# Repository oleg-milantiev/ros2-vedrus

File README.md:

# ros2-vedrus
ROS2 Vedrusohod bot sources

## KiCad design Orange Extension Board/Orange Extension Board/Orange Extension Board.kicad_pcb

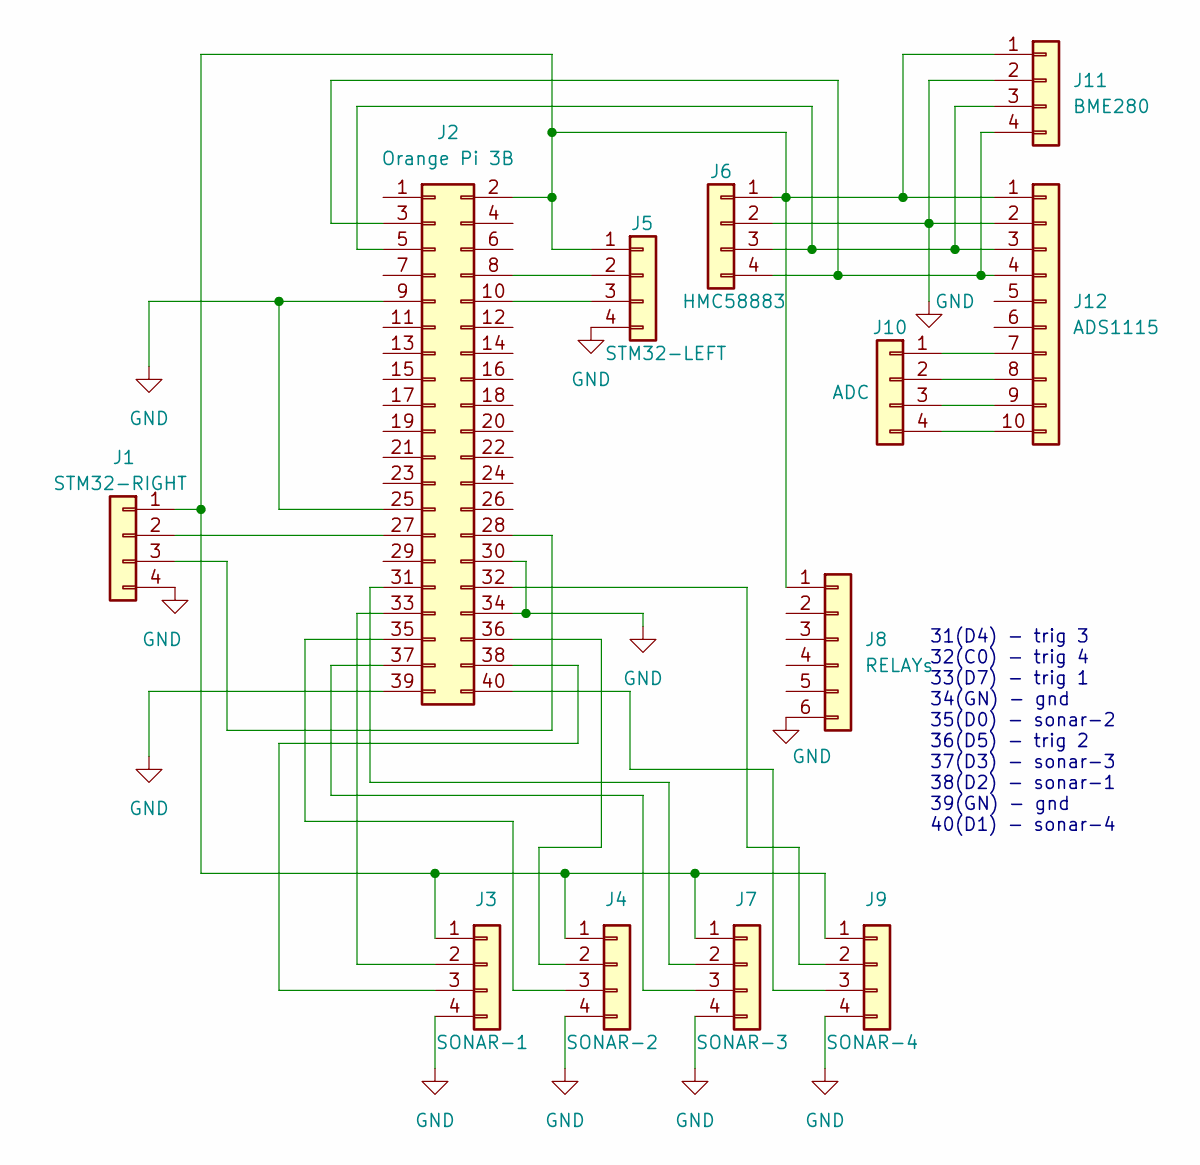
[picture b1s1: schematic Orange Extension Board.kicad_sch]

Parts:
J1: STM32-RIGHT; PinHeader_1x04_P2.54mm_Vertical
J2: Orange Pi 3B; PinHeader_2x20_P2.54mm_Vertical
J3: SONAR-1; PinHeader_1x04_P2.54mm_Vertical
J4: SONAR-2; PinHeader_1x04_P2.54mm_Vertical
J5: STM32-LEFT; PinHeader_1x04_P2.54mm_Vertical
J6: HMC58883; PinHeader_1x04_P2.54mm_Vertical
J7: SONAR-3; PinHeader_1x04_P2.54mm_Vertical
J8: RELAYs; PinHeader_1x06_P2.54mm_Vertical
J9: SONAR-4; PinHeader_1x04_P2.54mm_Vertical
J10: ADC; PinHeader_1x04_P2.54mm_Vertical
J11: BME280; PinHeader_1x04_P2.54mm_Vertical
J12: ADS1115; PinHeader_1x10_P2.54mm_Vertical

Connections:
GND: J1.4, J2.9, J2.25, J2.30, J2.34, J2.39, J3.4, J4.4, J5.4, J6.2, J7.4, J8.6, J9.4, J11.2, J12.2
unnamed: J1.1, J2.2, J3.1, J4.1, J5.1, J6.1, J7.1, J8.1, J9.1, J11.1, J12.1
unnamed: J1.2, J2.27
unnamed: J1.3, J2.28
unnamed: J2.3, J6.4, J11.4, J12.4
unnamed: J2.5, J6.3, J11.3, J12.3
unnamed: J2.8, J5.2
unnamed: J2.10, J5.3
unnamed: J2.32, J9.2
unnamed: J2.33, J3.2
unnamed: J2.40, J9.3
unnamed: J2.38, J3.3
unnamed: J2.36, J4.2
unnamed: J2.35, J4.3
unnamed: J2.31, J7.2
unnamed: J2.37, J7.3
unnamed: J10.1, J12.7
unnamed: J10.2, J12.8
unnamed: J10.3, J12.9
unnamed: J10.4, J12.10

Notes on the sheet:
31(D4) - trig 3 32(C0) - trig 4 33(D7) - trig 1 34(GN) - gnd 35(D0) - sonar-2 36(D5) - trig 2 37(D3) - sonar-3 38(D2) - sonar-1 39(GN) - gnd 40(D1) - sonar-4

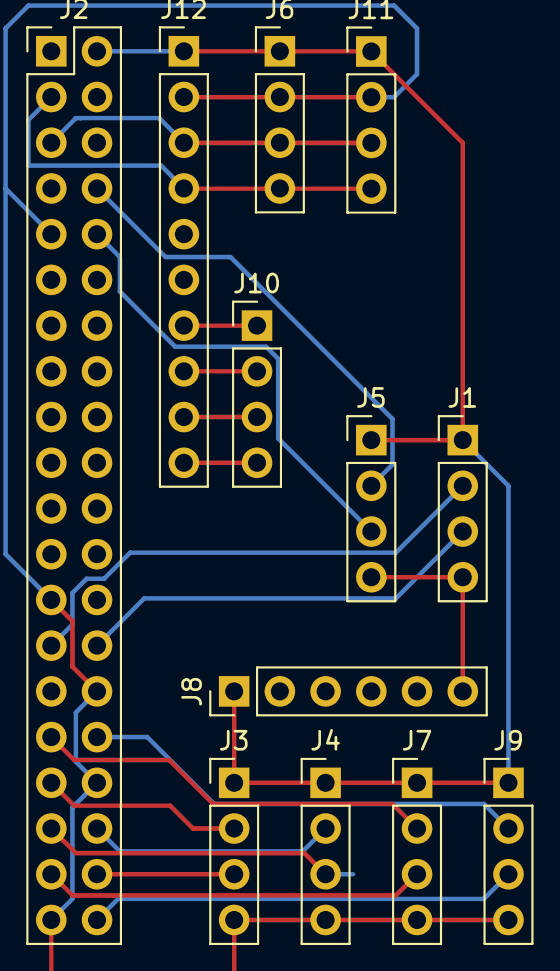
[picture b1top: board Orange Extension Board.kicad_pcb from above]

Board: 2 copper layers, 12 parts (0 on the bottom side), 20 nets.

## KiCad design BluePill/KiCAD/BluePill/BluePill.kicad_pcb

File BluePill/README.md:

# Blue Pill DC Motor Controller

This project implements a DC motor controller using the STM32F103C8T6 (Blue Pill) board. It features hardware quadrature encoder support, PID control, and serial communication for real-time control and monitoring.

## Features

- Hardware quadrature encoder support using STM32 Timer3
- 4x resolution encoder counting (both edges of both channels)
- PID-based motor speed control
- Serial communication at 115200 baud
- Real-time status reporting
- Configurable motor direction and speed
- Speed control in encoder ticks per second
- Hardware debouncing for reliable encoder readings

## Hardware Requirements

- STM32F103C8T6 (Blue Pill) board
- DC motor with quadrature encoder
- Motor driver (capable of DIR/PWM control)
- USB-to-Serial adapter (if not built into your programmer)

## Pin Connections

### Encoder
- Encoder A → PA6 (Timer3 Channel 1)
- Encoder B → PA7 (Timer3 Channel 2)

### Motor Control
- Direction → PA1
- PWM → PA2
- Brake → PA0 (TBD)

## Included Files

1. `Blink.ino` - Firmware for board testing
2. `BluePill.ino` - Main motor controller firmware
3. `Encoder.ino` - Test firmware for encoder verification
   - Supports one encoder:
     - Encoder 1: Timer3 (PA6/PA7)

## Software Requirements

1. Arduino IDE
2. STM32 board package for Arduino
3. PID_v1 library

## Installation

1. Install Arduino IDE from [arduino.cc](https://www.arduino.cc/en/software)
2. Install STM32 board package:
   https://github.com/stm32duino/Arduino_Core_STM32/wiki/Getting-Started
   - Open Arduino IDE
   - Go to Tools → Board → Boards Manager
   - Search for "STM32"
   - Install "STM32 MCU based boards"

3. Install PID Library:
   - Go to Tools → Manage Libraries
   - Search for "PID"
   - Install "PID" by Brett Beauregard

4. Configure Board Settings:
   - Board: "Generic STM32F103C series"
   - Upload Method: Your preferred method (ST-Link, Serial, etc.)
   - CPU Speed: "72MHz (Normal)"

5. Board Programming:
   - Set Boot0 jumper to 1
   - Connect board to computer
   - Press reset button on the board to prepare for upload
   - Click upload button in Arduino IDE
   - Set Boot0 jumper back to 0 (testing can be done without this step)

## Usage

### Serial Commands

The controller accepts the following commands through serial port at 115200 baud:

- `S` - Stop motor (sets target speed to 0)
- `M[speed]` - Move at specified speed (speed value depends on encoder resolution)
  - Positive values move forward
  - Negative values move reverse
  - Example: `M5` sets speed to 5 units forward
  - Example: `M-5` sets speed to 5 units reverse
- `X[max_pwm]` - Set maximum PWM value
  - Example: `X15` sets the maximum PWM value to 15

### Python Control Script

The project includes a Python script (`serial_control.py`) for easy motor control:

- Press 'S' to stop the motor
- Press '0-9' to set different speed levels (multiplied by 5)
- Press 'Q' to quit the program
- Real-time status messages are displayed automatically

To run the script:
```bash
python3 serial_control.py
```

### Status Messages

The controller sends status messages every 50ms in the following format:
```
SIDE,POS:[position],SPD:[current_speed],TGT:[target_speed],PWR:[motor_power],MAX_PWM:[max_pwm]
```

Where:
- `SIDE`: "VEDL" for left motor, "VEDR" for right motor
- `position`: Current encoder position (signed value, centered at 32767)
- `current_speed`: Actual speed in ticks/second
- `target_speed`: Commanded speed
- `motor_power`: PWM output (-PWR_MAX to PWR_MAX)
- `max_pwm`: Current maximum PWM value

## Hardware Configuration

- Encoder resolution: 8192 ticks per wheel revolution
- Maximum PWM value: 10
- Speed calculation interval: 50ms
- LED indication: PC13 lights up when speed exceeds half of encoder resolution

## Testing Encoder Hardware

The `Encoder.ino` firmware can be used to verify proper encoder operation:

1. Upload `Encoder.ino` to the BluePill
2. Open Serial Monitor at 115200 baud
3. Rotate encoder manually or using motor
4. Monitor the position values
   - Format: Single number representing encoder position
   - Values are centered around 0 (internally offset from 32767)
   - Positive values indicate one direction of rotation
   - Negative values indicate opposite direction
   - Updates every 100ms

Example output:
```
Hardware Encoder Test Started
Format: Encoder_Position
-123
-145
-160
0
42
85
```

Note: The position counter uses Timer3 in hardware quadrature mode with 4x resolution (counting both edges of both channels). The encoder connects to PA6 (Timer3 Channel 1) and PA7 (Timer3 Channel 2).

## PID Tuning

The default PID values are:
- Kp = 0.5
- Ki = 0.3
- Kd = 0.1

You may need to adjust these values based on your specific setup. To tune:
1. Start with all values at 0
2. Increase Kp until you get a reasonable response
3. Increase Ki to eliminate steady-state error
4. Add Kd to reduce overshoot if necessary

## Troubleshooting

1. **Motor doesn't move**:
   - Check power connections
   - Verify motor driver connections
   - Ensure PWM and DIR pins are correctly connected

2. **Encoder readings are erratic**:
   - Verify encoder connections match the Timer channels
   - Check encoder power supply
   - Ensure proper grounding
   - Verify encoder pull-up resistors are enabled

3. **Position counts in wrong direction**:
   - Swap encoder A and B connections
   - Or invert the motor power polarity

## License

This project is released under the MIT License. Feel free to use, modify, and distribute as needed.

---

# Контроллер двигателя постоянного тока на базе Blue Pill

Этот проект реализует контроллер двигателя постоянного тока с использованием платы STM32F103C8T6 (Blue Pill). Он включает в себя аппаратную поддержку квадратурного энкодера, ПИД-регулирование и последовательную связь для управления и мониторинга в реальном времени.

## Возможности

- Аппаратная поддержка квадратурного энкодера с использованием таймера STM32 Timer3
- Счетчик энкодера с 4-кратным разрешением (обе грани обоих каналов)
- ПИД-регулирование скорости двигателя
- Последовательная связь на скорости 115200 бод
- Отчеты о состоянии в реальном времени
- Настраиваемое направление и скорость двигателя
- Управление скоростью в тиках энкодера в секунду
- Аппаратное подавление дребезга для надежного считывания энкодера

## Аппаратные требования

- Плата STM32F103C8T6 (Blue Pill)
- Двигатель постоянного тока с квадратурным энкодером
- Драйвер двигателя (с управлением DIR/PWM)
- USB-Serial адаптер (если не встроен в программатор)
  (подключение https://microkontroller.ru/stm32-projects/nachalo-raboty-s-stm32-blue-pill-s-pomoshhyu-arduino-ide/ )

## Подключение выводов

### Энкодер
- Энкодер A → PA6 (Timer3 Channel 1)
- Энкодер B → PA7 (Timer3 Channel 2)

### Управление двигателем
- Направление → PA1
- ШИМ → PA2
- Тормоз → PA0 (TBD)

## Файлы в проекте

1. `Blink.ino` - Прошивка для проверки работы платы
2. `BluePill.ino` - Основная прошивка контроллера двигателя
3. `Encoder.ino` - Тестовая прошивка для проверки работы энкодера
   - Поддерживает один энкодер:
     - Энкодер 1: Timer3 (PA6/PA7)

## Программные требования

1. Arduino IDE
2. Пакет плат STM32 для Arduino
3. Библиотека PID_v1

## Установка

1. Установите Arduino IDE с [arduino.cc](https://www.arduino.cc/en/software)
2. Установите пакет плат STM32:
   https://github.com/stm32duino/Arduino_Core_STM32/wiki/Getting-Started
   - Откройте Arduino IDE
   - Перейдите в Инструменты → Плата → Менеджер плат
   - Найдите "STM32"
   - Установите "STM32 MCU based boards"

3. Установите библиотеку PID:
   - Перейдите в Инструменты → Управление библиотеками
   - Найдите "PID"
   - Установите "PID" от Brett Beauregard

4. Настройте параметры платы:
   - Плата: "Generic STM32F103C series"
   - Метод загрузки: Предпочитаемый метод (ST-Link, Serial и т.д.)
   - Частота CPU: "72MHz (Normal)"

5. Прошивка платы:
   - Переключить джампер Boot0 в 1
   - Подключить плату к компьютеру
   - Кнопкой сброса на плате подготовить плату к загрузке
   - Нажать кнопку загрузки в Arduino IDE
   - Переключить джампер Boot0 в 0 (тестировать можно без этого шага)

## Использование

### Команды последовательного порта

Контроллер принимает следующие команды через последовательный порт на скорости 115200 бод:

- `S` - Остановка двигателя (устанавливает целевую скорость в 0)
- `M[скорость]` - Движение с указанной скоростью (значение зависит от разрешения энкодера)
  - Положительные значения - движение вперед
  - Отрицательные значения - движение назад
  - Пример: `M5` устанавливает скорость 5 единиц вперед
  - Пример: `M-5` устанавливает скорость 5 единиц назад
- `X[max_pwm]` - Установить максимальное значение ШИМ
  - Пример: `X15` устанавливает максимальное значение ШИМ на 15

### Скрипт управления на Python

В проект включен Python-скрипт (`serial_control.py`) для удобного управления двигателем:

- Нажмите 'S' для остановки двигателя
- Нажмите '0-9' для установки различных уровней скорости (умножается на 5)
- Нажмите 'Q' для выхода из программы
- Сообщения о состоянии отображаются автоматически в реальном времени

Для запуска скрипта:
```bash
python3 serial_control.py
```

### Аппаратная конфигурация

- Разрешение энкодера: 8192 тика на оборот колеса
- Максимальное значение ШИМ: 10
- Интервал расчета скорости: 50мс
- Светодиодная индикация: PC13 загорается, когда скорость превышает половину разрешения энкодера

### Status Messages

The controller sends status messages every 50ms in the following format:
```
SIDE,POS:[position],SPD:[current_speed],TGT:[target_speed],PWR:[motor_power],MAX_PWM:[max_pwm]
```

Где:
- `SIDE`: "VEDL" для левого мотора, "VEDR" для правого мотора
- `position`: Текущая позиция энкодера (знаковое значение, центрировано на 32767)
- `current_speed`: Фактическая скорость в тиках в секунду
- `target_speed`: Заданная скорость
- `motor_power`: Выход ШИМ (от -PWR_MAX до PWR_MAX)
- `max_pwm`: Текущее максимальное значение ШИМ

## Тестирование энкодеров

Прошивка `Encoder.ino` может быть использована для проверки правильной работы энкодеров:

1. Загрузите `Encoder.ino` в BluePill
2. Откройте монитор порта на скорости 115200 бод
3. Вращайте энкодер вручную или с помощью двигателя
4. Отслеживайте значения позиций энкодера
   - Формат: Single number representing encoder position
   - Значения центрированы вокруг 0 (внутренне смещены от 32767)
   - Положительные значения указывают на одно направление вращения
   - Отрицательные значения указывают на противоположное направление
   - Обновляется каждые 100мс

Пример вывода:
```
Hardware Encoder Test Started
Format: Encoder_Position
-123
-145
-160
0
42
85
```

Примечание: Счетчик позиций использует Timer3 в режиме прямого квадратурного кодирования с 4x разрешением (подсчет обоих фронтов обоих каналов). Энкодер подключен к PA6 (Timer3 Channel 1) и PA7 (Timer3 Channel 2).

## Настройка ПИД-регулятора

Значения ПИД-регулятора по умолчанию:
- Kp = 0.5
- Ki = 0.3
- Kd = 0.1

Возможно, потребуется настроить эти значения под вашу конкретную установку. Для настройки:
1. Начните со всех значений равных 0
2. Увеличивайте Kp, пока не получите приемлемый отклик
3. Увеличивайте Ki для устранения статической ошибки
4. Добавьте Kd для уменьшения перерегулирования, если необходимо

## Устранение неполадок

1. **Двигатель не вращается**:
   - Проверьте подключение питания
   - Проверьте подключение драйвера двигателя
   - Убедитесь, что выводы ШИМ и DIR правильно подключены

2. **Показания энкодера нестабильны**:
   - Проверьте соответствие подключения энкодера каналам таймера
   - Проверьте питание энкодера
   - Обеспечьте правильное заземление
   - Проверьте включение подтягивающих резисторов

3. **Счетчик позиции работает в неправильном направлении**:
   - Поменяйте местами подключение выводов A и B энкодера
   - Или измените полярность питания двигателя

## Лицензия

Этот проект распространяется под лицензией MIT. Вы можете свободно использовать, изменять и распространять его по необходимости.

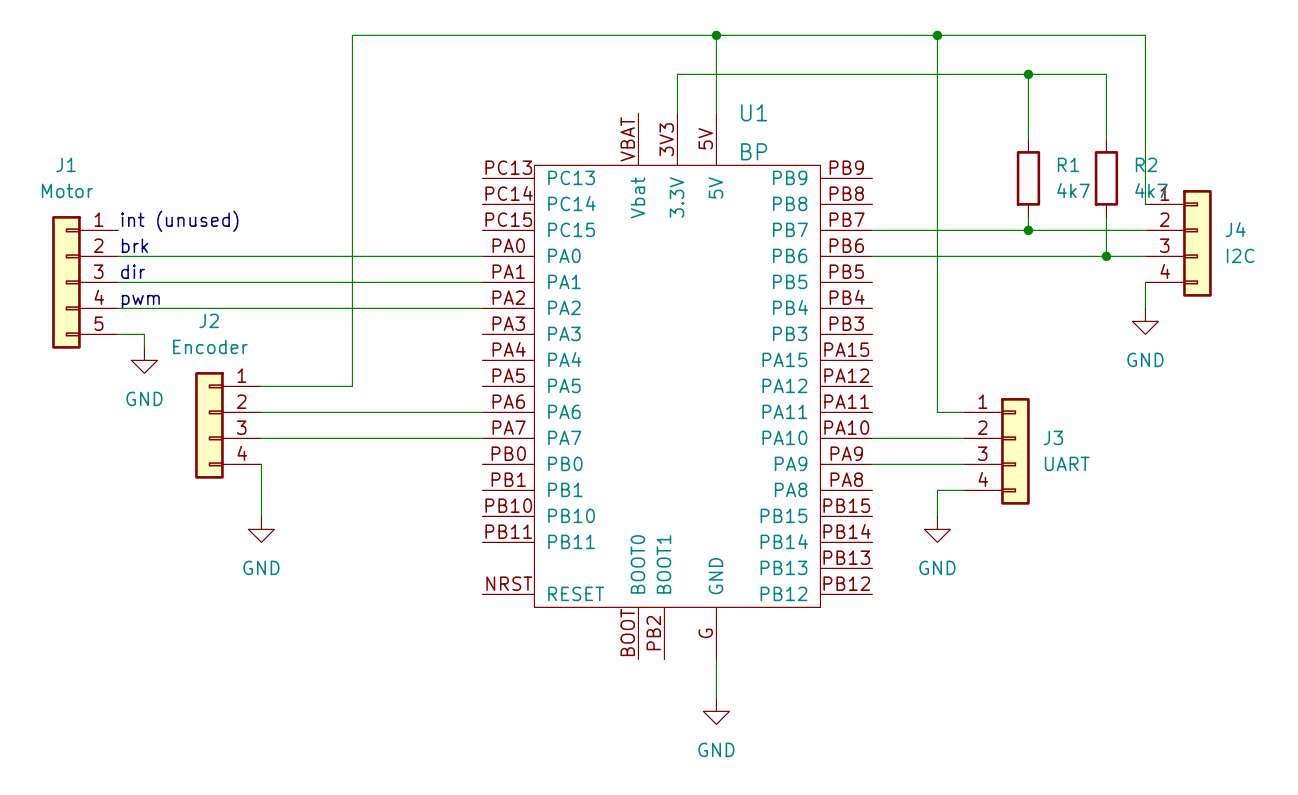
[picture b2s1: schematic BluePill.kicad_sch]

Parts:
J1: Motor; PinHeader_1x05_P2.54mm_Vertical
J2: Encoder; PinHeader_1x04_P2.54mm_Vertical
J3: UART; PinHeader_1x04_P2.54mm_Vertical
J4: I2C; PinHeader_1x04_P2.54mm_Vertical
R1, R2: 4k7; R_Axial_DIN0204_L3.6mm_D1.6mm_P2.54mm_Vertical
U1: BP; blue_pill

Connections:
GND: J1.5, J2.4, J3.4, J4.4, U1.G (GND)
unnamed: J1.2, U1.PA0
unnamed: J1.3, U1.PA1
unnamed: J1.4, U1.PA2
unnamed: J2.1, J3.1, J4.1, U1.5V
unnamed: J2.2, U1.PA6
unnamed: J2.3, U1.PA7
unnamed: J3.2, U1.PA10
unnamed: J3.3, U1.PA9
unnamed: J4.2, R1.2, U1.PB7
unnamed: J4.3, R2.2, U1.PB6
unnamed: R1.1, R2.1, U1.3V3 (3.3V)

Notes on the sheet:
int (unused)
pwm
dir
brk

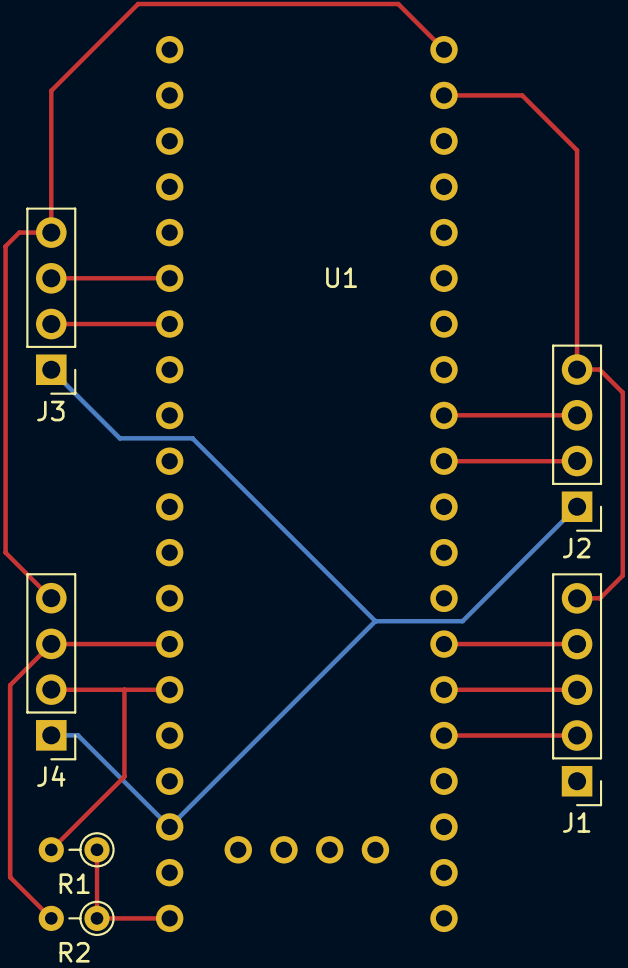
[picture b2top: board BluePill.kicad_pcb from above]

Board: 2 copper layers, 7 parts (0 on the bottom side), 12 nets.

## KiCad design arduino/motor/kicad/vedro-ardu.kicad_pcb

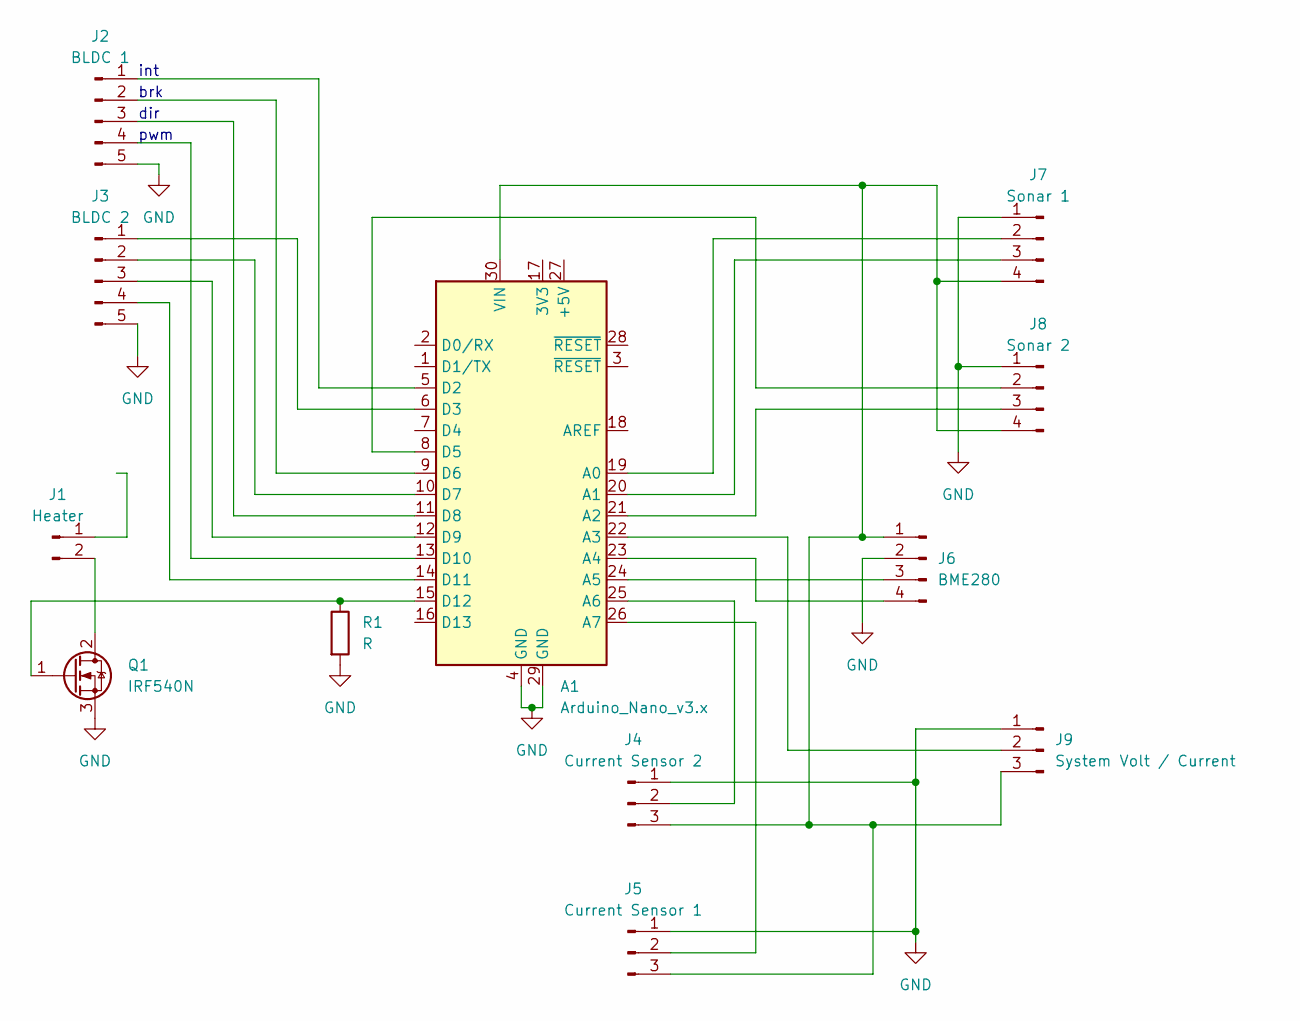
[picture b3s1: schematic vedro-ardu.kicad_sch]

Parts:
A1: Arduino_Nano_v3.x; Arduino_Nano
J1: Heater; PinHeader_1x02_P2.54mm_Vertical
J2: BLDC 1; PinHeader_1x05_P2.54mm_Vertical
J3: BLDC 2; PinHeader_1x05_P2.54mm_Vertical
J4: Current Sensor 2; PinHeader_1x03_P2.54mm_Vertical
J5: Current Sensor 1; PinHeader_1x03_P2.54mm_Vertical
J6: BME280; PinHeader_1x04_P2.54mm_Vertical
J7: Sonar 1; PinHeader_1x04_P2.54mm_Vertical
J8: Sonar 2; PinHeader_1x04_P2.54mm_Vertical
J9: System Volt / Current; PinHeader_1x03_P2.54mm_Vertical
Q1: IRF540N; TO-220-3_Vertical
R1: R; R_0805_2012Metric

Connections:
GND: A1.4 (GND), A1.29 (GND), J2.5, J3.5, J4.1, J5.1, J6.2, J7.1, J8.1, J9.1, Q1.3 (S), R1.2
unnamed: A1.5 (D2), J2.1
unnamed: A1.6 (D3), J3.1
unnamed: A1.8 (D5), J8.2
unnamed: A1.9 (D6), J2.2
unnamed: A1.10 (D7), J3.2
unnamed: A1.11 (D8), J2.3
unnamed: A1.12 (D9), J3.3
unnamed: A1.13 (D10), J2.4
unnamed: A1.14 (D11), J3.4
unnamed: A1.15 (D12), Q1.1 (G), R1.1
unnamed: A1.19 (A0), J7.2
unnamed: A1.21 (A2), J8.3
unnamed: A1.22 (A3), J9.2
unnamed: A1.23 (A4), J6.4
unnamed: A1.24 (A5), J6.3
unnamed: A1.25 (A6), J4.2
unnamed: A1.26 (A7), J5.2
unnamed: A1.30 (VIN), J4.3, J5.3, J6.1, J7.4, J8.4, J9.3
unnamed: J1.2, Q1.2 (D)
unnamed: A1.20 (A1), J7.3

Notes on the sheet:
pwm
dir
brk
int

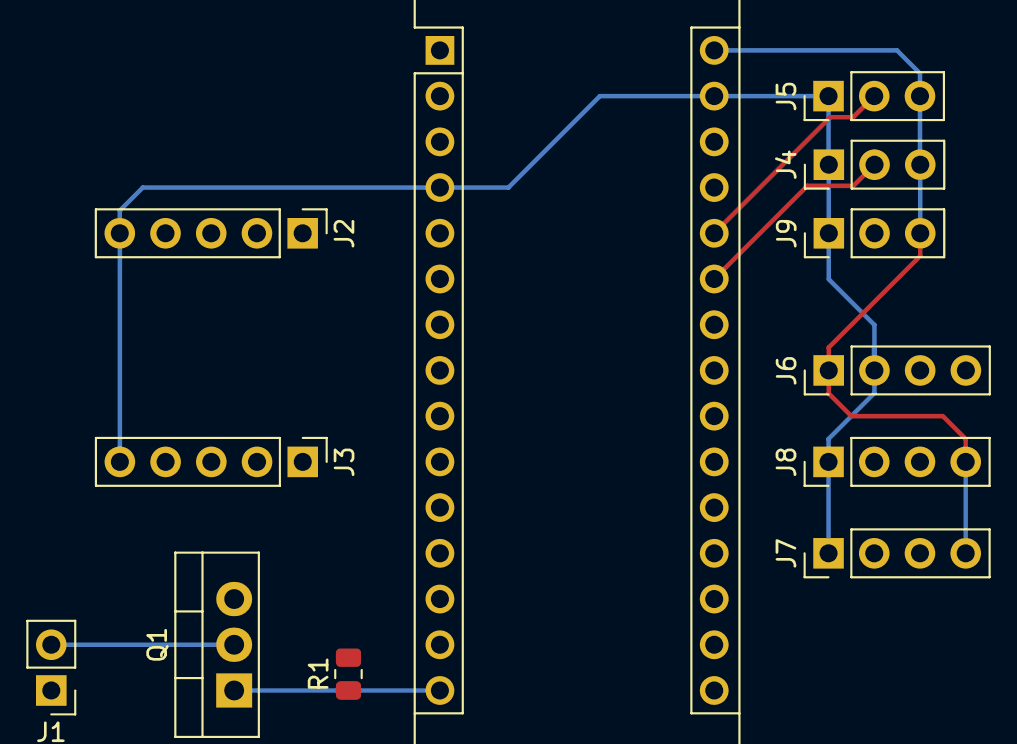
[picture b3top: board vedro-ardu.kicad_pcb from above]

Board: 2 copper layers, 12 parts (0 on the bottom side), 21 nets.

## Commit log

2024-02-06 Init
2024-02-07 Start to separate left / right ardu nodes
2024-02-09 Auto detect ardu sides. Keyboard test controller
2024-02-13 Gyro RC
2024-02-14 Kanzas city ports shuffle
2024-02-14 Arduino devices
2024-02-15 Intel RealSense docker - working image
2024-02-17 RealSense ... integrating
2024-02-17 ROS2 install in packages on Ubuntu
2024-02-17 draft
2024-02-18 Move to Ubuntu on host and package-style ROS2
2024-02-25 YOLOv8 + RKNN
2024-02-26 YOLOv8 RKNN Solver - multiple cameras, frame rate, move allmost into parameters
2024-02-27 YOLOv8-RKNN - Multiple cameras
2024-02-28 Ardu - add power and dir into output
2024-02-28 Rewrite Ardu node for new interfaces
2024-02-28 Working launch: ardu x 2, usb webcam, realsense, yolo,
2024-02-29 Safety
2024-03-01 Safety node - working RGBD and Sonar
2024-03-02 USB Camera search
2024-03-02 Visualize graphs
2024-03-02 Improve solver and safety
2024-03-06 mixed up xyxy -> yxyx box coordinates
2024-03-06 Move Ardu serial read to asycn. Publish stable 5pfs
2024-03-07 Separate side motors controlling
2024-03-09 SpeedUp arduino firmware by less average ADC and sonar. Limit sonar to 150 cm
2024-03-09 Try to build CPP
2024-03-09 Ignore pycache
2024-03-09 Working influx logger
2024-03-09 Add simple-pid into installer
2024-03-09 Refactor launch*
2024-03-09 Async Serial. Motors PID regulators. Low cost CSV logger.
2024-03-13 Return to 16 count adc mean. No any improve :(
2024-03-13 Add Controller with task_safety_forward in. Add KeepAlive into Safety and Controller. Add Crash flag into Ardu motor control. Add Breaking flag into Ardu PID motor control.
2024-03-13 Add moving polarity to PID. Add new task_safety_rotate_to_person
2024-03-14 Stop engines! :)
2024-03-14 Add solver rate
2024-03-14 Minor improve logging
2024-03-14 New task: safety_rotate_move_to_person
2024-03-14 CSV. Graph. Minors
2024-03-15 HTTP server (for use with mobile) working draft. Show safety on canvas
2024-03-25 Return debug keyboard controller
2024-03-25 Ardu: PID now send motor command via ROS (to use info in server / remote controll)
2024-03-25 Greately improved remote (controller status, motors power and pid, graphics improvements)
2024-12-15 Start to move from atmega8 to stm32 (blue pill)
2024-12-17 Optimize bluepill code. Not tested yet!
2024-12-22 Debugging BluePill
2024-12-22 Precision error
2024-12-22 First alpha
2024-12-22 Actual
2024-12-22 Comment unused, but maybe useful in future median filtering
2024-12-22 Improve visual
2024-12-24 Comment
2024-12-26 Arduino 2 and I2C tests
2025-01-16 Sensors publishers
2025-01-16 BME280: test modifications
2025-01-16 beauty
2025-01-16 SOANRs: test modifications
2025-01-16 ADS1115: not ready yet
2025-01-16 ADS1115: preAlpha
2025-01-16 Voltage interface
2025-01-17 ADS1115: tested and working
2025-01-17 Sensors: Working in launch
2025-01-17 Bluepill: Workging node!
2025-01-17 Motor interfaces
2025-01-26 Add hmc5883l_ros2
2025-01-26 QMC588L node
2025-01-26 remove X view
2025-01-26 npu top
2025-02-01 Add sonar names
2025-02-01 Separate trig / echo pins in ros2 parameters
2025-02-01 Magnitometr node
2025-02-04 tests
2025-02-04 Remove I2C
2025-02-04 Extension board init
2025-02-04 Multicamera block 3D model
2025-02-04 actua
2025-02-07 3 USB cameras in they places
2025-02-07 Move realsense to /vedrus namespace
2025-02-07 Remove image saving (use ros2 utilities to do so)
2025-02-07 Deepseek deep optimize give ... 3% CPU :)
2025-02-16 Serial ports
2025-02-17 Remove deprecated ardu support
2025-02-17 Actualize keyboard controller
2025-02-17 Add nodes to launch.py
2025-02-17 Use vnc instead of remote x-server
2025-02-17 Add reverse parameter
2025-02-17 Add old-good crash signal to stop motors forever
2025-02-17 Update to new environment
2025-02-17 Split controller into parts by mode
2025-02-17 Enable safety and controller nodes
2025-02-17 VSCode ignores
2025-02-17 Debug
2025-02-18 Short testing launch environment
2025-02-18 new mode MoveFixed(incLeft, incRight)
2025-02-18 minor
2025-02-18 Add elapsed time calculate into message
2025-02-20 Grok's code to train YOLOv8 by YOLO-world created dataset
2025-02-20 Tested solver
2025-02-23 Try YOLOv11 model
2025-02-23 Try to optimize realsense fps and resolution
2025-02-23 Ignore non UTF characters at input
2025-02-23 Optimize speed, resolution and fps
2025-02-24 Reverse motor status
2025-02-24 Remove depth camera noise
2025-02-24 ModeMoveFixed is debugged
2025-02-25 Add max_pwm parameter and status
2025-02-25 Add sonar and realsense keepalives
2025-02-25 Fix: next move must be 20k
2025-02-25 Add four keepalives for motors, bearing and safety
2025-02-25 Add azimuths to sonar. Move to vedrus.Sonar
2025-02-26 Move to meters in Sonar messages
2025-02-26 Convert to spaces. Extend alarm log
2025-02-26 Correct pins. Short sonars test launch
2025-02-26 Correct pins. Up rate by 10 times! Median filter at 10 items window. Use edges detector decrease CPU load.
2025-02-26 Improve logging. Tune constants. ModeSafetyStop start from stopping motors
2025-02-26 Use meters in range
2025-02-26 Sync launche files
2025-02-28 Start to unDistort fisheyes
2025-03-04 Try to tune camera brightness
2025-03-04 Fast fisheye correction
2025-03-05 Try to prevent controller hangup
2025-03-05 Shorter max-pwm
2025-03-05 Ignore vscode inspect
2025-03-05 Try to resolve driver hangup
2025-03-09 Improved keys controller
2025-03-09 Save camera's images for dataset
2025-03-09 Try to find explose by self
2025-03-09 Exposure finder. Save images for dataset
2025-03-11 Remove unused launche files
2025-03-11 Sync resolution and fps
2025-03-12 Docker with NVIDIA CUDA: Start to build on laptop
2025-03-15 Docker ROS2 rolling with nvidia gpu
2025-03-18 Docker ROS2 with NVIDIA GPU
2025-03-19 Move to x64 with NVIDIA: Start to do
2025-03-21 ROS2 Jazzy
2025-03-21 Ultralytics YOLO-based resolve
2025-03-21 Optimize camera names. Use nvidia
2025-03-22 STM32 Two Motors
2025-03-23 Default isMoving=false to smooth robot start
2025-03-23 Actual schema (not a board)
2025-04-08 Working alpha
